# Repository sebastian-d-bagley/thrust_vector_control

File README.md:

# thrust_vector_control
Here are all the relevant files for my seventh iteration of a thrust vector controlled model rocket.

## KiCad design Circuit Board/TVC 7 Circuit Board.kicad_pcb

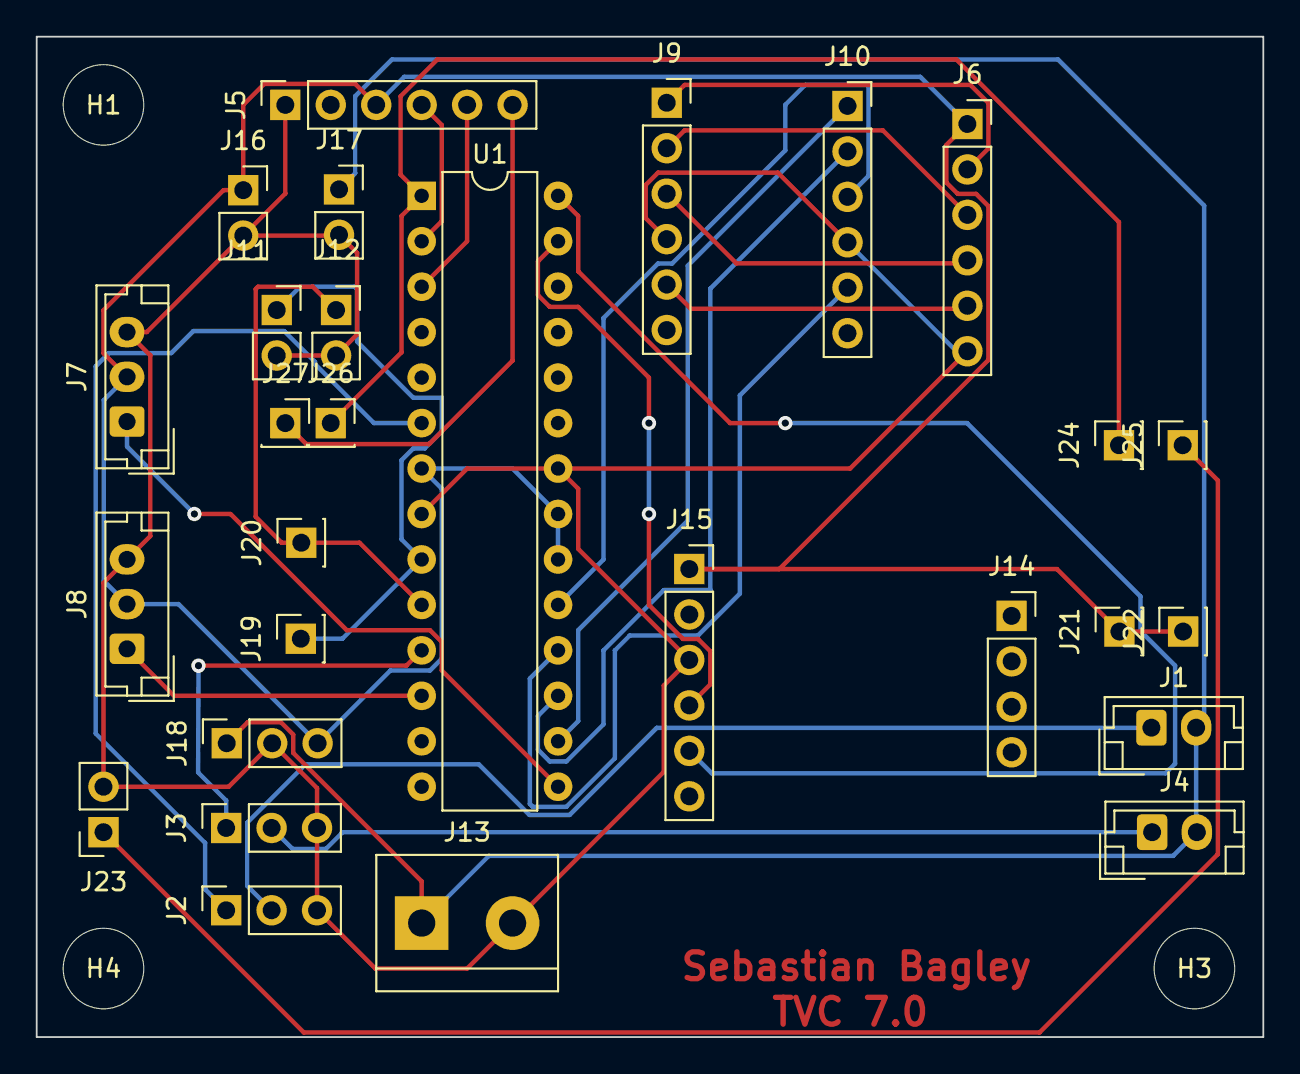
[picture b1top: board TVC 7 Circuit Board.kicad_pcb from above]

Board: 2 copper layers, 68.5 x 55.9 mm, 32 parts (0 on the bottom side), 26 nets.

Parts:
H1, H2, H3, H4: MountingHole; MountingHole_4.5mm
J1, J4: Conn_01x02_Female; JST_EH_B2B-EH-A_1x02_P2.50mm_Vertical
J2, J3, J18: Conn_01x03_Female; PinSocket_1x03_P2.54mm_Vertical
J5, J6, J9, J10: Conn_01x06_Pin; PinSocket_1x06_P2.54mm_Vertical
J7, J8: Conn_01x03_Male; JST_EH_B3B-EH-A_1x03_P2.50mm_Vertical
J11, J12, J16, J17, J23: Conn_01x02_Female; PinSocket_1x02_P2.54mm_Vertical
J13: Conn_01x02_Female; TerminalBlock_bornier-2_P5.08mm
J14: Conn_01x04_Female; PinSocket_1x04_P2.54mm_Vertical
J15: Conn_01x06_Female; PinSocket_1x06_P2.54mm_Vertical
J19, J20, J21, J22, J24, J25, J26, J27: Conn_01x01_Female; PinSocket_1x01_P2.54mm_Vertical
U1: ATmega328-P; DIP-28_W7.62mm

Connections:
unnamed: J1.1, J2.2
unnamed: J1.2, J4.2, J13.1, J17.1, J18.1
unnamed: J2.1, U1.6 (PD4)
unnamed: J3.1, U1.11 (PD5)
unnamed: J3.2, J4.1
unnamed: J5.4, U1.2 (PD0)
unnamed: J5.5, U1.3 (PD1)
unnamed: J6.2, J9.1
unnamed: J6.3, J9.2
unnamed: J6.4, J9.3
unnamed: J6.5, J9.5
unnamed: J7.1, U1.15 (PB1)
unnamed: J8.1, U1.12 (PD6)
unnamed: J10.1, U1.16 (PB2)
unnamed: J10.2, U1.17 (PB3)
unnamed: J10.3, U1.19 (PB5)
unnamed: J2.3, J3.3, J5.1, J6.6, J7.3, J8.3, J9.4, J10.4, J11.2, J12.2, J13.2, J15.3, J16.2, J17.2, J18.2, J23.2, U1.8 (GND), U1.22 (GND)
unnamed: J10.5, U1.18 (PB4)
unnamed: J11.1, J19.1, U1.9 (XTAL1/PB6)
unnamed: J12.1, J20.1, U1.10 (XTAL2/PB7)
unnamed: J5.3, J6.1, J7.2, J8.2, J15.1, J16.1, J18.3, J21.1, J22.1, U1.7 (VCC), U1.20 (AVCC), U1.21 (AREF)
unnamed: J15.4, U1.27 (PC4)
unnamed: J15.5, U1.28 (PC5)
unnamed: J23.1, J25.1
unnamed: J24.1, J26.1, U1.1 (~RESET/PC6)
unnamed: J5.6, J27.1

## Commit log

2024-12-08 Create CAD folder
2024-12-08 mount CAD upload
2024-12-08 circuit attachment cad
2024-12-08 Create folder circuit board
2024-12-08 circuit board files
2024-12-08 Create folder simulation
2024-12-08 simulink_files
